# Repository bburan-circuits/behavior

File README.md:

Revisions
---------
* 0.2: Fix bug in Q3 (load must be on drain side)
* 0.1: Initial version

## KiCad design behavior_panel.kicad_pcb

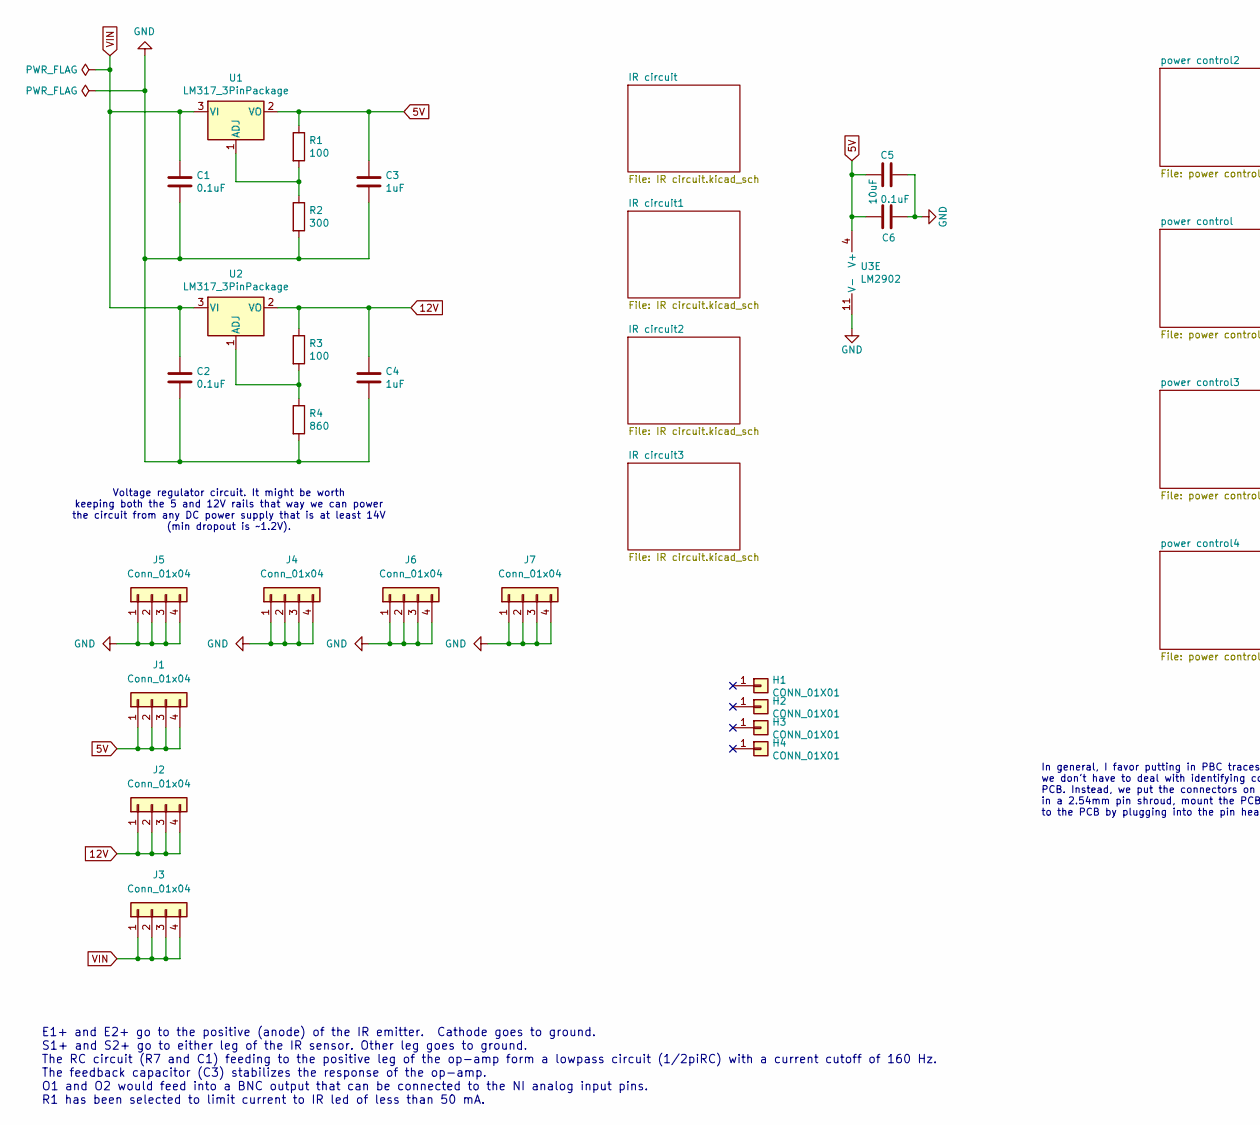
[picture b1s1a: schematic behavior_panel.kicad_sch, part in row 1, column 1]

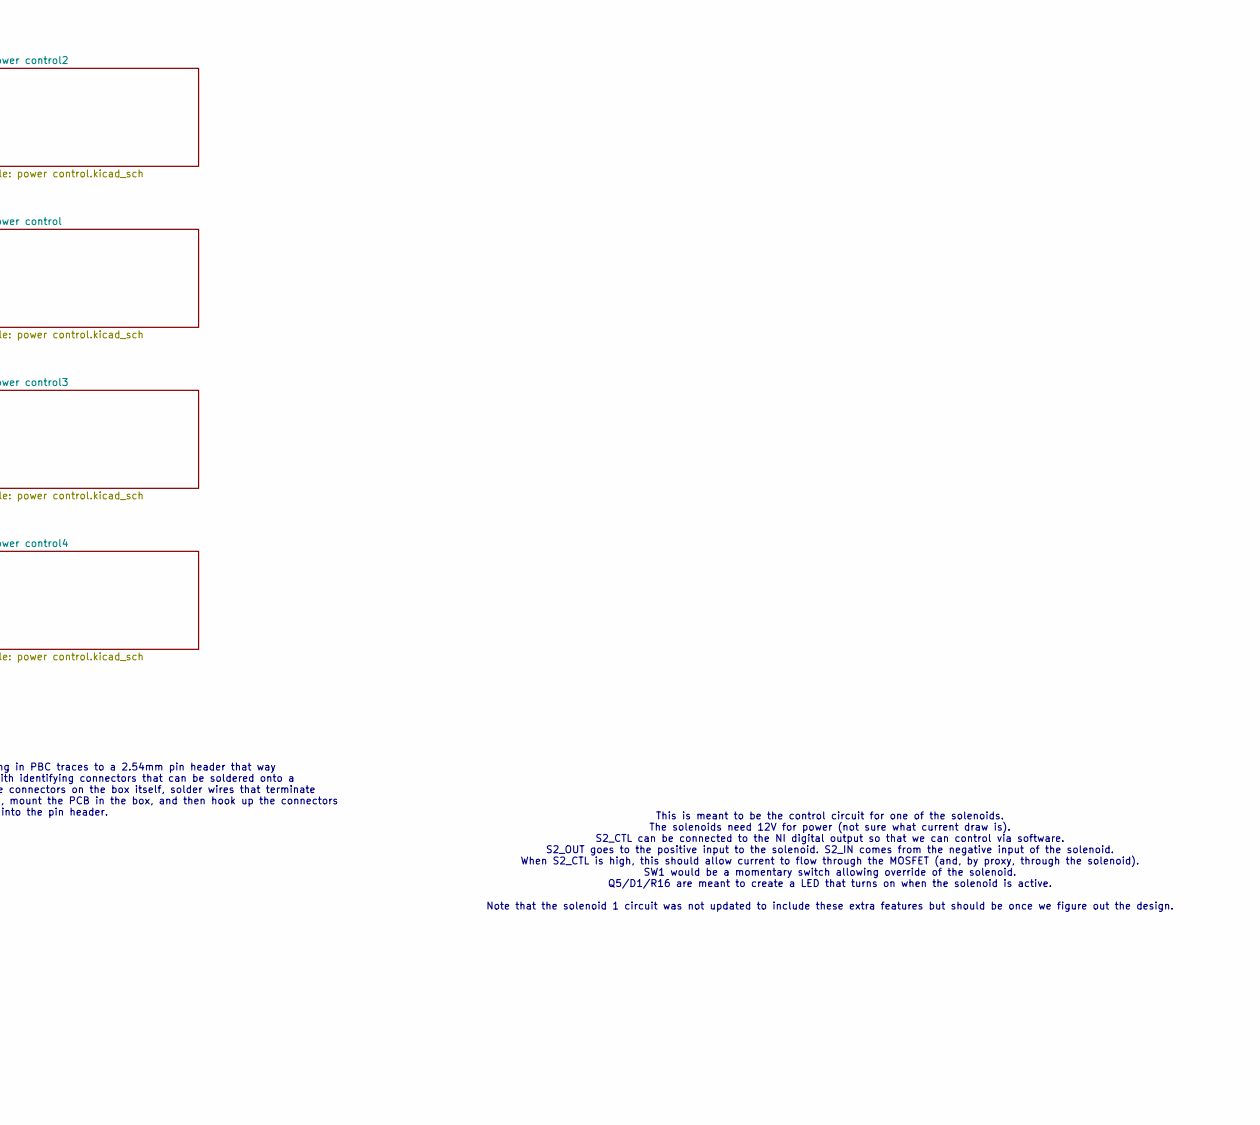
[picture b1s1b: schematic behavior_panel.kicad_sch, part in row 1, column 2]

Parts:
C1, C2: 0.1uF; C_Rect_L4.0mm_W2.5mm_P2.50mm; MPN C315C104M5U5TA
C3, C4: 1uF; C_Rect_L7.0mm_W3.5mm_P5.00mm; MPN MF-CAP-0603-1uF
C5: 10uF; C_Rect_L7.0mm_W3.5mm_P5.00mm; MPN MF-CAP-1206-10uF
C6: 0.1uF; C_Rect_L4.0mm_W2.5mm_P2.50mm; MPN MF-CAP-0603-0.1uF
H1, H2, H3, H4: CONN_01X01; MountingHole_3mm_Pad
J1, J2, J3, J4, J5, J6, J7: Conn_01x04; PinHeader_1x04_P2.54mm_Vertical
R1, R3: 100; R_Axial_DIN0207_L6.3mm_D2.5mm_P7.62mm_Horizontal; MPN MF-RES-0805-100
R2: 300; R_Axial_DIN0207_L6.3mm_D2.5mm_P7.62mm_Horizontal; MPN MF-RES-0805-220
R4: 860; R_Axial_DIN0207_L6.3mm_D2.5mm_P7.62mm_Horizontal; MPN MF-RES-0805-220
U1, U2: LM317_3PinPackage; TO-220-3_Vertical; MPN LM317AG-TN3-R; LCSC C75510
U3: LM2902; DIP-14_W7.62mm_LongPads; MPN TLV2774CPWR

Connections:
5V: C3.1, C5.2, C6.2, J1.1, J1.2, J1.3, J1.4, R1.1, U1.2 (VO), U3.4 (V+); also elsewhere on the board
12V: C4.1, J2.1, J2.2, J2.3, J2.4, R3.1, U2.2 (VO)
/IR circuit2/O: U3.8, U3.9 (-); also elsewhere on the board
/IR circuit3/O: U3.13 (-), U3.14; also elsewhere on the board
/IR circuit/O: U3.6 (-), U3.7; also elsewhere on the board
GND: C1.2, C2.2, C3.2, C4.2, C5.1, C6.1, J4.1, J4.2, J4.3, J4.4, J5.1, J5.2, J5.3, J5.4, J6.1, J6.2, J6.3, J6.4, J7.1, J7.2, J7.3, J7.4, R2.2, R4.2, U3.11 (V-); also elsewhere on the board
unnamed: R1.2, R2.1, U1.1 (ADJ)
unnamed: R3.2, R4.1, U2.1 (ADJ)
unnamed 42: U3.5 (+); also elsewhere on the board
unnamed 43: U3.10 (+); also elsewhere on the board
unnamed 44: U3.12 (+); also elsewhere on the board
VIN: C1.1, C2.1, J3.1, J3.2, J3.3, J3.4, U1.3 (VI), U2.3 (VI)

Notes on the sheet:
Voltage regulator circuit. It might be worth keeping both the 5 and 12V rails that way we can power the circuit from any DC power supply that is at least 14V (min dropout is ~1.2V).
In general, I favor putting in PBC traces to a 2.54mm pin header that way we don't have to deal with identifying connectors that can be soldered onto a PCB. Instead, we put the connectors on the box itself, solder wires that terminate in a 2.54mm pin shroud, mount the PCB in the box, and then hook 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
This is meant to be the control circuit for one of the solenoids. The solenoids need 12V for power (not sure what current draw is). S2_CTL can be connected to the NI digital output so that we can control via software. S2_OUT goes to the positive input to the solenoid. S2_IN comes from the negative 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
E1+ and E2+ go to the positive (anode) of the IR emitter. Cathode goes to ground. S1+ and S2+ go to either leg of the IR sensor. Other leg goes to ground. The RC circuit (R7 and C1) feeding to the positive leg of the op-amp form a lowpass circuit (1/2piRC) with a current cutoff of 160 Hz. The feedb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

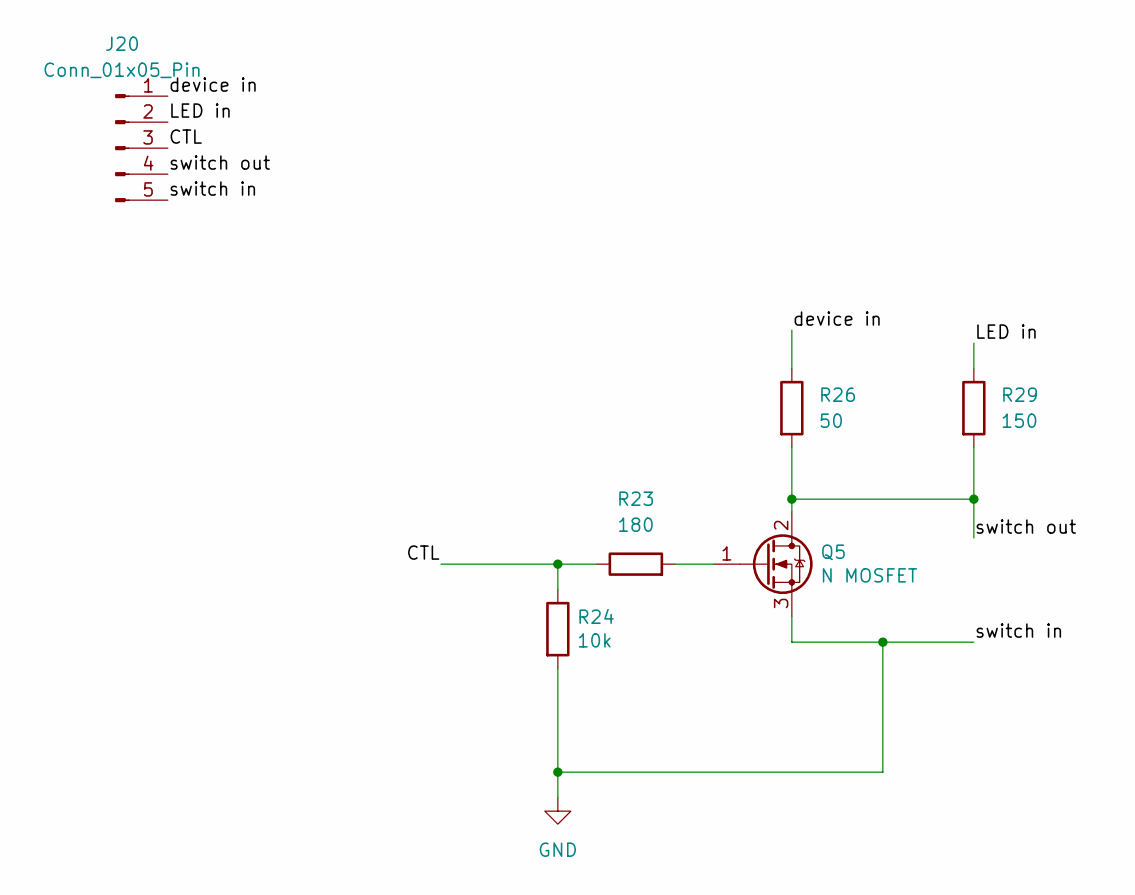
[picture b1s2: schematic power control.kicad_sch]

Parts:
J20: Conn_01x05_Pin; PinHeader_1x05_P2.54mm_Vertical
Q5: N MOSFET; TO-220-3_Vertical; MPN NVD5C668NLT4G
R23: 180; R_Axial_DIN0207_L6.3mm_D2.5mm_P7.62mm_Horizontal
R24: 10k; R_Axial_DIN0207_L6.3mm_D2.5mm_P7.62mm_Horizontal; MPN MF-RES-0402-10k
R26: 50; R_Axial_DIN0207_L6.3mm_D2.5mm_P7.62mm_Horizontal
R29: 150; R_Axial_DIN0207_L6.3mm_D2.5mm_P7.62mm_Horizontal

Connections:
/power control3/CTL: J20.3, R23.1, R24.1
/power control3/LED in: J20.2, R29.1
/power control3/device in: J20.1, R26.1
/power control3/switch out: J20.4, Q5.2 (D), R26.2, R29.2
GND: J20.5, Q5.3 (S), R24.2; also elsewhere on the board
unnamed: Q5.1 (G), R23.2

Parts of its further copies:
J17, J19, J22: Conn_01x05_Pin; PinHeader_1x05_P2.54mm_Vertical
Q1, Q3, Q7: N MOSFET; TO-220-3_Vertical; MPN NVD5C668NLT4G
R5, R16, R34: 180; R_Axial_DIN0207_L6.3mm_D2.5mm_P7.62mm_Horizontal
R6, R17, R35: 10k; R_Axial_DIN0207_L6.3mm_D2.5mm_P7.62mm_Horizontal; MPN MF-RES-0402-10k
R8, R19, R37: 50; R_Axial_DIN0207_L6.3mm_D2.5mm_P7.62mm_Horizontal
R11, R22, R40: 150; R_Axial_DIN0207_L6.3mm_D2.5mm_P7.62mm_Horizontal

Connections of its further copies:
/power control2/CTL: J19.3, R16.1, R17.1
/power control2/LED in: J19.2, R22.1
/power control2/device in: J19.1, R19.1
/power control2/switch out: J19.4, Q3.2 (D), R19.2, R22.2
/power control4/CTL: J22.3, R34.1, R35.1
/power control4/LED in: J22.2, R40.1
/power control4/device in: J22.1, R37.1
/power control4/switch out: J22.4, Q7.2 (D), R37.2, R40.2
/power control/CTL: J17.3, R5.1, R6.1
/power control/LED in: J17.2, R11.1
/power control/device in: J17.1, R8.1
/power control/switch out: J17.4, Q1.2 (D), R8.2, R11.2
GND: J17.5, J19.5, J22.5, Q1.3 (S), Q3.3 (S), Q7.3 (S), R6.2, R17.2, R35.2; also elsewhere on the board
unnamed: Q1.1 (G), R5.2
unnamed: Q3.1 (G), R16.2
unnamed: Q7.1 (G), R34.2

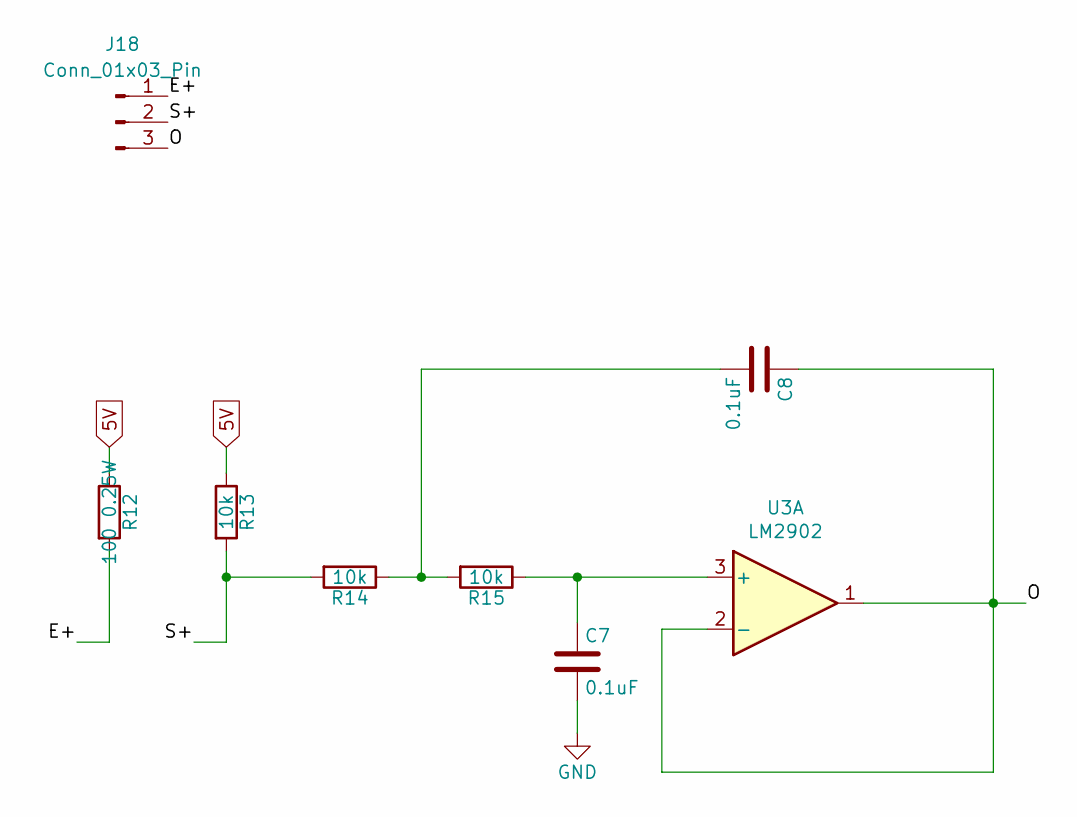
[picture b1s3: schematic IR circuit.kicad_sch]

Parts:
C7, C8: 0.1uF; C_Rect_L4.0mm_W2.5mm_P2.50mm; MPN MF-CAP-0603-0.1uF
J18: Conn_01x03_Pin; PinHeader_1x03_P2.54mm_Vertical
R12: 100 0.25W; R_Axial_DIN0207_L6.3mm_D2.5mm_P7.62mm_Horizontal; MPN Panasonic ERJ-P08J101V
R13, R14, R15: 10k; R_Axial_DIN0207_L6.3mm_D2.5mm_P7.62mm_Horizontal; MPN MF-RES-0402-10k
U3: LM2902; DIP-14_W7.62mm_LongPads; MPN TLV2774CPWR

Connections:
5V: R12.1, R13.1; also elsewhere on the board
/IR circuit1/E+: J18.1, R12.2
/IR circuit1/O: C8.1, J18.3, U3.1, U3.2 (-)
/IR circuit1/S+: J18.2, R13.2, R14.2
/IR circuit2/O: U3.8, U3.9 (-); also elsewhere on the board
/IR circuit3/O: U3.13 (-), U3.14; also elsewhere on the board
/IR circuit/O: U3.6 (-), U3.7; also elsewhere on the board
GND: C7.2; also elsewhere on the board
unnamed: C8.2, R14.1, R15.2
unnamed: C7.1, R15.1, U3.3 (+)
unnamed 42: U3.5 (+); also elsewhere on the board
unnamed 43: U3.10 (+); also elsewhere on the board
unnamed 44: U3.12 (+); also elsewhere on the board

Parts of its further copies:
C9, C10, C11, C12, C13, C14: 0.1uF; C_Rect_L4.0mm_W2.5mm_P2.50mm; MPN MF-CAP-0603-0.1uF
J21, J23, J24: Conn_01x03_Pin; PinHeader_1x03_P2.54mm_Vertical
R30, R41, R45: 100 0.25W; R_Axial_DIN0207_L6.3mm_D2.5mm_P7.62mm_Horizontal; MPN Panasonic ERJ-P08J101V
R31, R32, R33, R42, R43, R44, R46, R47, R48: 10k; R_Axial_DIN0207_L6.3mm_D2.5mm_P7.62mm_Horizontal; MPN MF-RES-0402-10k

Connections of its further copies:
5V: R30.1, R31.1, R41.1, R42.1, R45.1, R46.1; also elsewhere on the board
/IR circuit2/E+: J23.1, R41.2
/IR circuit2/O: C12.1, J23.3; also elsewhere on the board
/IR circuit2/S+: J23.2, R42.2, R43.2
/IR circuit3/E+: J24.1, R45.2
/IR circuit3/O: C14.1, J24.3; also elsewhere on the board
/IR circuit3/S+: J24.2, R46.2, R47.2
/IR circuit/E+: J21.1, R30.2
/IR circuit/O: C10.1, J21.3; also elsewhere on the board
/IR circuit/S+: J21.2, R31.2, R32.2
GND: C9.2, C11.2, C13.2; also elsewhere on the board
unnamed: C10.2, R32.1, R33.2
unnamed: C12.2, R43.1, R44.2
unnamed: C14.2, R47.1, R48.2
unnamed 42: C9.1, R33.1; also elsewhere on the board
unnamed 43: C11.1, R44.1; also elsewhere on the board
unnamed 44: C13.1, R48.1; also elsewhere on the board

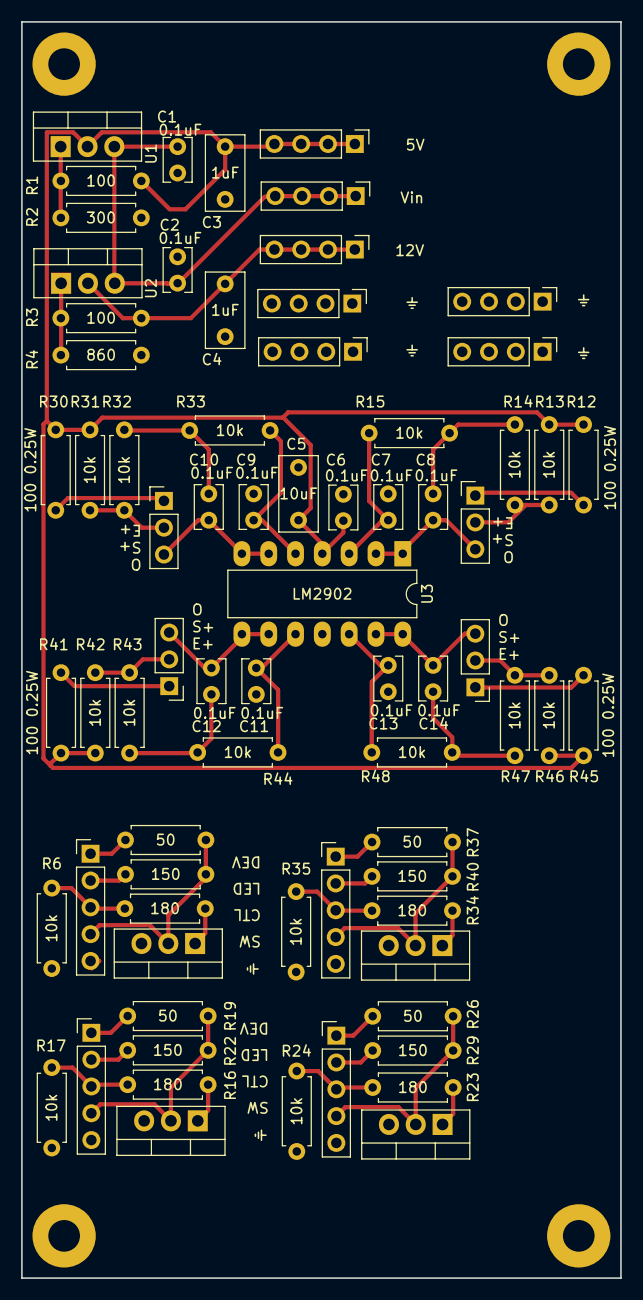
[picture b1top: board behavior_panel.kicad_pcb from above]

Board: 2 copper layers, 56.8 x 119.0 mm, 76 parts (0 on the bottom side), 46 nets.

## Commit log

2020-01-28 Initial behavior circuit schematic
2020-02-14 Fix bug in MOSFET light control
2022-07-08 Update to Kicad 6
2024-03-06 Add documentation to schematic
2024-03-06 Add gerber files
2024-04-16 Updated to include four power relays and four IR circuts
    Went back to the through-hole, hand-solderable version.
2024-09-04 Update connectors to be smaller
2024-09-10 Release of V2 of behavior panel
    * LED indicators should now be working
    * Slightly narrower board
    * Added recommended values for footprints
2025-02-11 Add more ground pins. Fix labels.
2025-02-11 Add documentation re IR circuit
